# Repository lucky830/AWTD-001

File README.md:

# Autonomous Warehouse Transport Droid-001

## What is this project about?
An autonomous warehouse transport robot (prototype) for a final year school project

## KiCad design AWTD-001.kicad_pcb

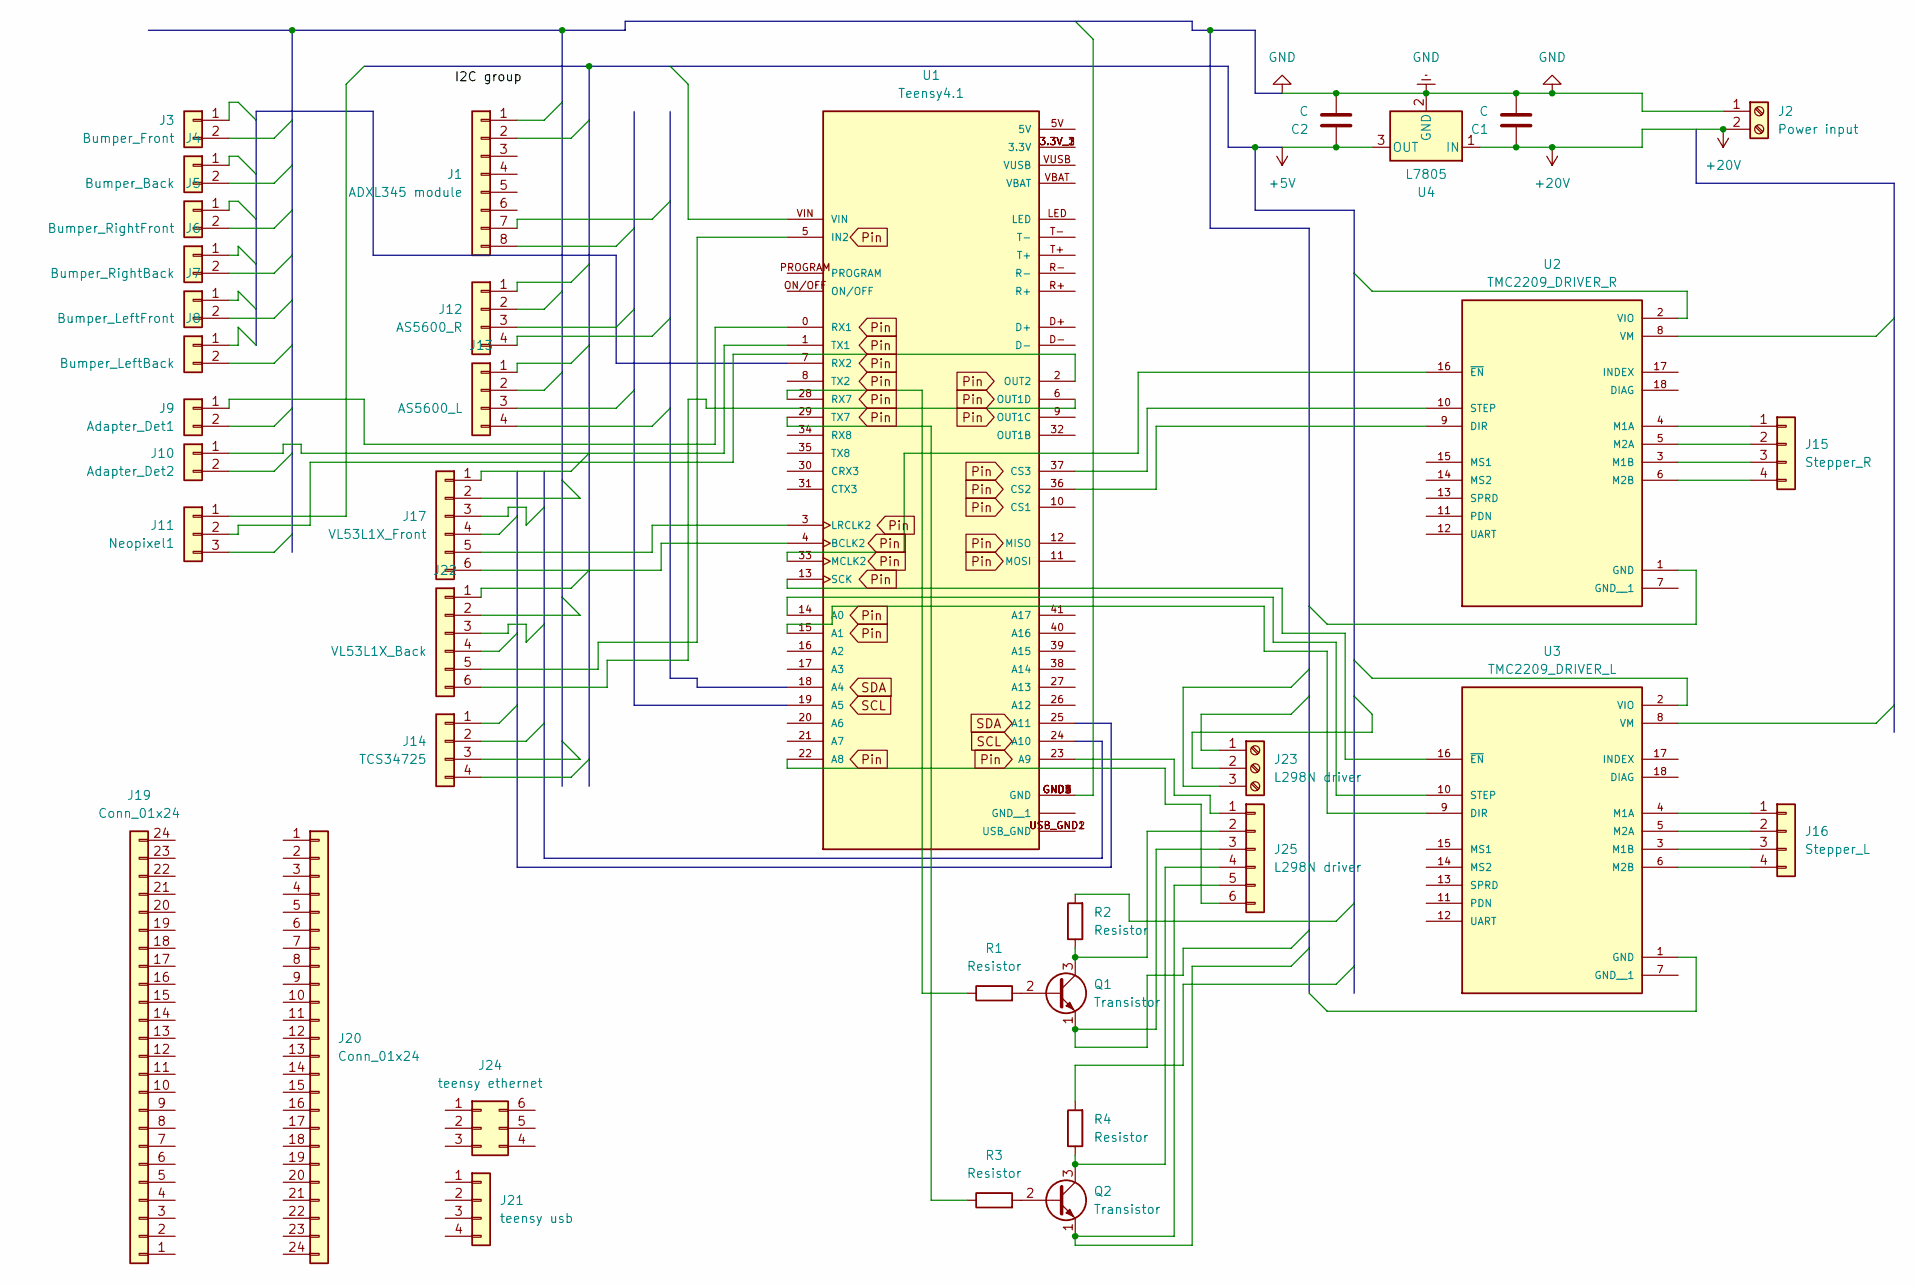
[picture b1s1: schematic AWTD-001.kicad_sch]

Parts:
C1, C2: C; C_Radial_D5.0mm_H5.0mm_P2.00mm
J1: ADXL345 module; JST_XH_B8B-XH-A_1x08_P2.50mm_Vertical
J2: Power input; TerminalBlock_Phoenix_MPT-0,5-2-2.54_1x02_P2.54mm_Horizontal
J3: Bumper_Front; JST_XH_B2B-XH-A_1x02_P2.50mm_Vertical
J4: Bumper_Back; JST_XH_B2B-XH-A_1x02_P2.50mm_Vertical
J5: Bumper_RightFront; JST_XH_B2B-XH-A_1x02_P2.50mm_Vertical
J6: Bumper_RightBack; JST_XH_B2B-XH-A_1x02_P2.50mm_Vertical
J7: Bumper_LeftFront; JST_XH_B2B-XH-A_1x02_P2.50mm_Vertical
J8: Bumper_LeftBack; JST_XH_B2B-XH-A_1x02_P2.50mm_Vertical
J9: Adapter_Det1; JST_XH_B2B-XH-A_1x02_P2.50mm_Vertical
J10: Adapter_Det2; JST_XH_B2B-XH-A_1x02_P2.50mm_Vertical
J11: Neopixel1; JST_XH_B3B-XH-A_1x03_P2.50mm_Vertical
J12: AS5600_R; JST_XH_B4B-XH-A_1x04_P2.50mm_Vertical
J13: AS5600_L; JST_XH_B4B-XH-A_1x04_P2.50mm_Vertical
J14: TCS34725; JST_XH_B4B-XH-A_1x04_P2.50mm_Vertical
J15: Stepper_R; JST_XH_B4B-XH-A_1x04_P2.50mm_Vertical
J16: Stepper_L; JST_XH_B4B-XH-A_1x04_P2.50mm_Vertical
J17: VL53L1X_Front; JST_XH_B6B-XH-A_1x06_P2.50mm_Vertical
J19, J20: Conn_01x24; PinHeader_1x24_P2.54mm_Vertical
J21: teensy usb; JST_XH_B4B-XH-A_1x04_P2.50mm_Vertical
J22: VL53L1X_Back; JST_XH_B6B-XH-A_1x06_P2.50mm_Vertical
J23: L298N driver; TerminalBlock_Phoenix_MPT-0,5-3-2.54_1x03_P2.54mm_Horizontal
J24: teensy ethernet; PinHeader_2x03_P2.54mm_Vertical
J25: L298N driver; JST_XH_B6B-XH-A_1x06_P2.50mm_Vertical
Q1, Q2: Transistor; TO-92_Inline
R1, R2, R3, R4: Resistor; R_Axial_DIN0204_L3.6mm_D1.6mm_P7.62mm_Horizontal
U1: Teensy4.1; PARTREV 4.1
U2: TMC2209_DRIVER_R; TMC2209_StepperDriver; PARTREV 1.20
U3: TMC2209_DRIVER_L; TMC2209_StepperDriver; PARTREV 1.20
U4: L7805; TO-220-3_Vertical

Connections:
+5V: C2.1, U4.3 (OUT)
+20V: C1.1, J2.2, U4.1 (IN)
GND: C1.2, C2.2, J2.1, U4.2 (GND)
unnamed: J9.1 (PIN), U1.0 (RX1)
unnamed: J10.1 (PIN), U1.1 (TX1)
unnamed: J11.2 (Data), U1.2 (OUT2)
unnamed: J15.1 (1A), U2.4 (M1A)
unnamed: J15.3 (1B), U2.3 (M1B)
unnamed: J15.2 (2A), U2.5 (M2A)
unnamed: J15.4 (2B), U2.6 (M2B)
unnamed: J16.1 (1A), U3.4 (M1A)
unnamed: J16.3 (1B), U3.3 (M1B)
unnamed: J16.2 (2A), U3.5 (M2A)
unnamed: J16.4 (2B), U3.6 (M2B)
unnamed: J17.5 (GPIO1), U1.3 (LRCLK2)
unnamed: J17.6 (XSHUT), U1.4 (BCLK2)
unnamed: J22.5 (GPIO1), U1.5 (IN2)
unnamed: J22.6 (XSHUT), U1.6 (OUT1D)
unnamed: J25.2 (DIR1A), Q1.3 (C), R2.1
unnamed: J25.4 (DIR1B), Q2.3 (C), R4.1
unnamed: J25.3 (DIR2A), Q1.1 (E)
unnamed: J25.5 (DIR2B), Q2.1 (E)
unnamed: J25.1 (ENA), U1.23 (A9)
unnamed: J25.6 (ENB), U1.22 (A8)
unnamed: Q1.2 (B), R1.2
unnamed: Q2.2 (B), R3.2
unnamed: U1.3.3V_1 (3.3V), U1.3.3V_2 (3.3V), U1.3.3V_3 (3.3V)
unnamed: U1.14 (A0), U3.10 (STEP)
unnamed: U1.15 (A1), U3.9 (DIR)
unnamed: U1.36 (CS2), U2.9 (DIR)
unnamed: U1.37 (CS3), U2.10 (STEP)
unnamed: U1.GND1 (GND), U1.GND2 (GND), U1.GND3 (GND), U1.GND4 (GND), U1.GND5 (GND)
unnamed: U1.33 (MCLK2), U2.16 (~EN)
unnamed: R1.1, U1.28 (RX7)
unnamed: U1.13 (SCK), U3.16 (~EN)
unnamed: R3.1, U1.29 (TX7)
unnamed: U1.USB_GND1 (USB_GND), U1.USB_GND2 (USB_GND)

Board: 2 copper layers, 37 parts (0 on the bottom side), 37 nets, no tracks yet.

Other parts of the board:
J13#2: AS5600_L; JST_XH_B4B-XH-A_1x04_P2.50mm_Vertical

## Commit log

2025-10-09 Update README.md
    Project name change
2025-10-09 Update README.md
    correct text layout
2025-10-09 Update README.md
    edit
2025-10-21 Fix capitalization in project title
2025-11-11 Initial commit
    Schematic V1
    PCB not yet begun
